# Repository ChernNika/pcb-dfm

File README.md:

# PCB DFM

Анализатор технологичности печатных плат для KiCad 10. Проверяет ширину дорожек, зазоры, пояски отверстий и паяльную маску. Для участков с острыми углами оценивает риск избыточного травления. Результат — HTML-отчёт с отмеченными на плате проблемными местами.

## Установка плагина на Windows

1. Установите **KiCad 10** и **Python 3.11 или новее**. Для установки плагина и его первого запуска нужен интернет.
2. На странице проекта в GitHub нажмите зелёную кнопку **Code → Download ZIP**. В Проводнике щёлкните по скачанному архиву правой кнопкой мыши и выберите **Извлечь всё…**
3. Откройте распакованную папку, в которой рядом с `install.bat` лежат папки `dfm` и `plugin`. Дважды щёлкните `install.bat` и дождитесь сообщения **«Готово»**. Установщик возьмёт файлы плагина из этой папки.
4. Откройте в KiCad **Настройки → Параметры → Плагины**, включите **сервер IPC API** и перезапустите KiCad.

## Первая проверка

1. В редакторе печатных плат KiCad откройте свою плату или [пример b1_demo.kicad_pcb](boards/demo/b1_demo.kicad_pcb) из папки `boards/demo`.
2. На панели редактора нажмите **Проверить технологичность**. В браузере выберите профиль **«Открытые данные»** и нажмите **Проверить**.
3. После анализа откроется отчёт. Нажмите метку на схеме платы, чтобы перейти к описанию находки. Если у находки есть кнопка **Показать в KiCad**, она выделит соответствующий объект в редакторе.

## Выход годных плат

Нажмите **Проверить**. Плагин возьмёт текущее состояние платы из KiCad, выгрузит медные слои Gerber и сверловку Excellon и включит их в HTML-отчёт. При открытии отчёта появится расчётный выход годных по площадкам и проводникам для выбранного профиля производства.

Раскройте **Контактные площадки и каплевидные переходы**, выберите слой и площадку на карте или в списке. Рядом появятся её размеры, проверка пояска и соединения, вероятность годности. Кнопка **Подставить размеры в модель отверстия** позволяет на той же странице изменить геометрию и сравнить обычную и каплевидную площадки.

Для своего комплекта файлов откройте **Проверить свой комплект Gerber** на стартовой странице. Загрузите слои меди и металлизированную сверловку отдельными файлами или ZIP-архивом и нажмите **Рассчитать**.

## Запуск из PowerShell

После установки выполните из папки проекта:

```powershell
& "$env:USERPROFILE\.venvs\pcb-dfm\Scripts\python.exe" -m dfm check boards/demo/b1_demo.kicad_pcb --open
```

Вместо демоплаты можно указать свой файл `.kicad_pcb` или путь к папке с файлами Gerber и сверловки.

[Лицензия MIT](LICENSE)

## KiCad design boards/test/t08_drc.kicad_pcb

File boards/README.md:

# Тестовые платы

- `test/` — свои тестовые платы ядра (шаг 1.6), каждая на одну тонкость модели. Генерируются
  скриптом `make_boards.py` (писатель плат `dfm/board/kicad_writer.py`); зоны заливает сам KiCad.
- `demo/` — демо-платы из документов по классам, переведённые в `.kicad_pcb`. На них заранее
  известно, какие дефекты есть и где (`*.json` рядом: подписи ситуаций в мм, ось Y вверх).
  Это эталон для проверки правил в пункте 2. Сейчас: B1 (Л1–Л8), A7 (М1–М8), A3 (К1–К7);
  A5 (З1–З8). `a3_demo` — 4 слоя со стеком, у которого глубины слоёв как в документе (0; 0,2; 1,4; 1,6 мм),
  капля у V6 строится самим KiCad при перезаливке, микроотверстие M1, площадка J2 со смещением.
  `a5_demo` — вскрытия строит KiCad по правилам `.kicad_dru` (от готового отверстия), V6
  сдвигается ПОСЛЕ заливки (`a5_after_refill`) — устаревшая заливка; земля поля BGA — глухие
  переходные F.Cu → In1.Cu.
- `kicad_demos/` — демо-проекты из поставки KiCad 10 берутся прямо из `share/kicad/demos`.
- `open/` — открытые проекты с GitHub и других площадок; для каждого нужно указать источник и лицензию.

```powershell
python boards/make_boards.py                      # пересоздать test/ и demo/ (нужен KiCad для заливки зон)
python -m dfm compare boards/test/*.kicad_pcb -o out   # сверка: два пути + нарушения против DRC KiCad
```

| Плата | Что проверяет |
|---|---|
| `t01_pads37` | все формы площадок (прямоугольник, скруглённый, срезанные углы, трапеция, овал, круг, произвольные, выводные, NPTH, краевой разъём) на компоненте под 37° сверху и под −110° снизу; отступы маски площадки, компонента, платы, отрицательные |
| `t02_arcs` | дорожки-дуги 30°…270°, радиусы 0,6…10 мм, цепочка отрезок–дуга–отрезок, дуги графики и контура |
| `t03_vias` | 6 слоёв: сквозное, глухие сверху и снизу, скрытое, микроотверстия; закрытие маской |
| `t04_padstacks` | падстеки front_inner_back и custom, заданные полностью и частично (форма, размер, доля скругления, смещение) |
| `t05_unused` | удаление неиспользуемых площадок: дорожка, зона (подключение вычисляет KiCad), ничего |
| `t06_zones` | термобарьеры, сплошное и без подключения, сетчатая заливка, приоритеты, островки, область запрета, зона в компоненте |
| `t07_outline` | контур с вырезом-пазом, вырезы (круг, скруглённый прямоугольник, многоугольник, паз в компоненте), вторая плата в заготовке |
| `t08_drc` | 12 случаев зазоров при пороге 0,2 мм: дорожка–дорожка, –площадка, площадка–площадка, переходное, дуга, край платы, касания, пересечение, графика без цепи; пары рядом с порогом без нарушения |
| `t09_a1` | дефекты класса A1 известного размера (Д1–Д5, Д7, Д8); напряжения, токи и таблица зазоров — тестовый профиль `t09_a1_profile.toml` (`tests/test_a1.py`) |

Что выяснилось на этих платах о KiCad 10.0 (учтено в адаптере, проверено по Gerber):

- слой падстека от основной формы **ничего не наследует**: без формы — круг, без размера — площадки
  нет, без доли скругления — 0, без смещения — 0; в режиме front_inner_back незаданный B.Cu
  берёт форму Inner;
- у падстека custom окно маски — **круг** диаметром по ширине основной площадки в центре отверстия;
- DRC не проверяет зазоры и касания медной графики без цепи;
- зону-каплю, записанную вручную, `kicad-cli` при перезаливке **удаляет** и строит капли заново
  по настройке `(teardrops … (enabled yes))` каждого отверстия;
- стек без слоёв шелкографии и пасты KiCad принимает в плату, но в job-файл Gerber **толщины
  слоёв не пишет** — писатель плат выводит стек полностью;
- проверка «ширина пояска» DRC учитывает смещение площадки (`offset`) и стек площадки — как A3;
- вскрытие в заливке вокруг отверстия без площадки на слое KiCad строит от **готового** отверстия:
  Ø = d + 2·зазор (а ствол — сверло d + 2t_мет); правила `.kicad_dru` (`clearance`,
  `hole_clearance`, с условием на цепь, класс цепей и слой) заливка учитывает.

Выгрузки `kicad-cli` (Gerber, сверловка, отчёты DRC) складываются в папку отчёта `compare`
и в git не попадают.

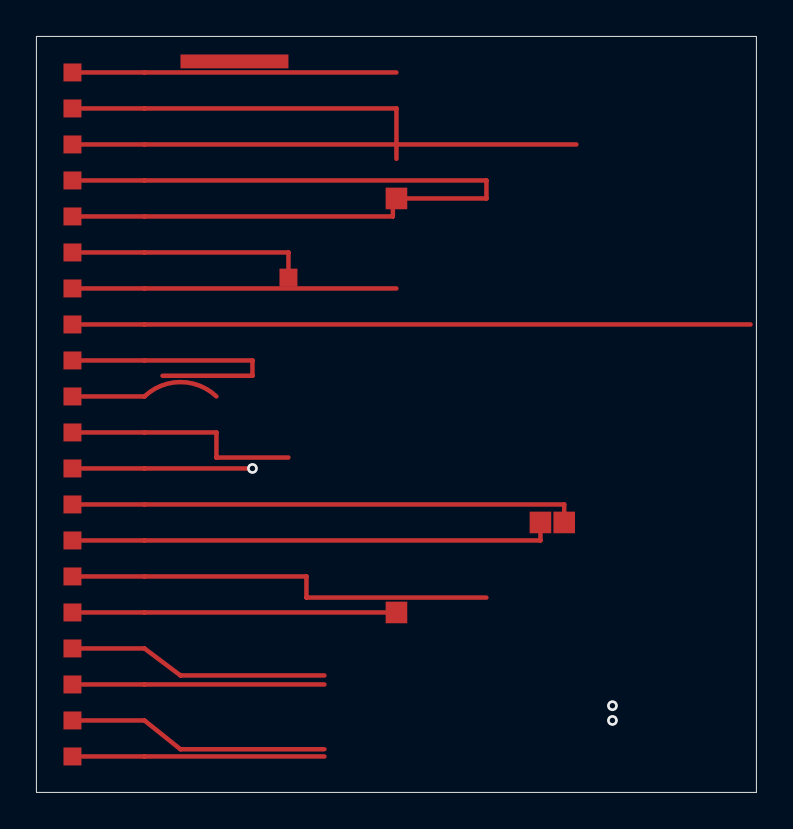
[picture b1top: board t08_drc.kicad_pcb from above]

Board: 2 copper layers, 40.0 x 42.0 mm, 6 parts (0 on the bottom side), 5 nets.

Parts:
J1: J1
R1: R1
R2: R2
R3: R3
R4: R4
R5: R5

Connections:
S4: J1.5, R1.1
S6: J1.7, R2.1
S7: J1.8, R3.1
S14: J1.15, R4.1
S16: J1.17, R5.1

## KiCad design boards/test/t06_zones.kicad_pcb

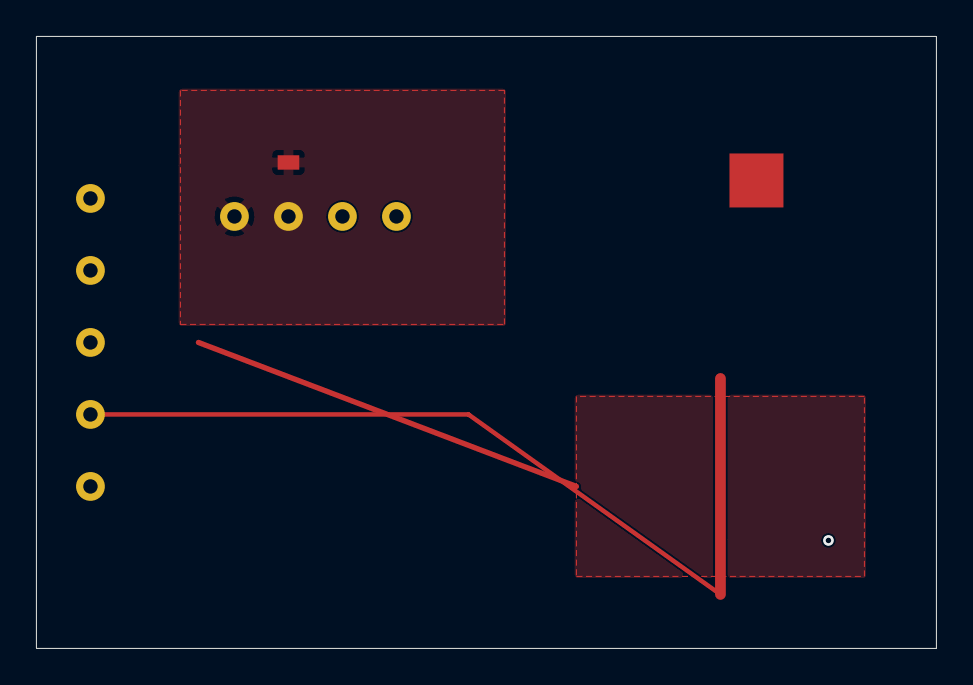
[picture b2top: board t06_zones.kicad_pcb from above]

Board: 4 copper layers, 50.0 x 34.0 mm, 3 parts (0 on the bottom side), 3 nets.

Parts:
J1: J1
Q1: Q1
U1: U1

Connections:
GND: J1.1, U1.1, U1.2, U1.3, U1.4
P2: J1.3, Q1.1
S: J1.5, U1.5
